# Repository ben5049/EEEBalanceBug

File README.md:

# EEEBalanceBug

### Abstract
A two-wheeled balancing robot was created to map a maze autonomously and calculate the shortest path. The maze was bounded by LED strips, and up to 3 differently coloured beacons could be placed around the maze beforehand. The beacons must be powered through a carefully optimised DC grid by solar power. There was a budget of £60 for the robot. An FPGA-based camera system must be used. Other optical sensors were permitted, but no other cameras. The methods employed include designing an advanced embedded system, hardware-based image processing, scalable cloud infrastructure and optimal energy distribution systems.

### Gantt Chart

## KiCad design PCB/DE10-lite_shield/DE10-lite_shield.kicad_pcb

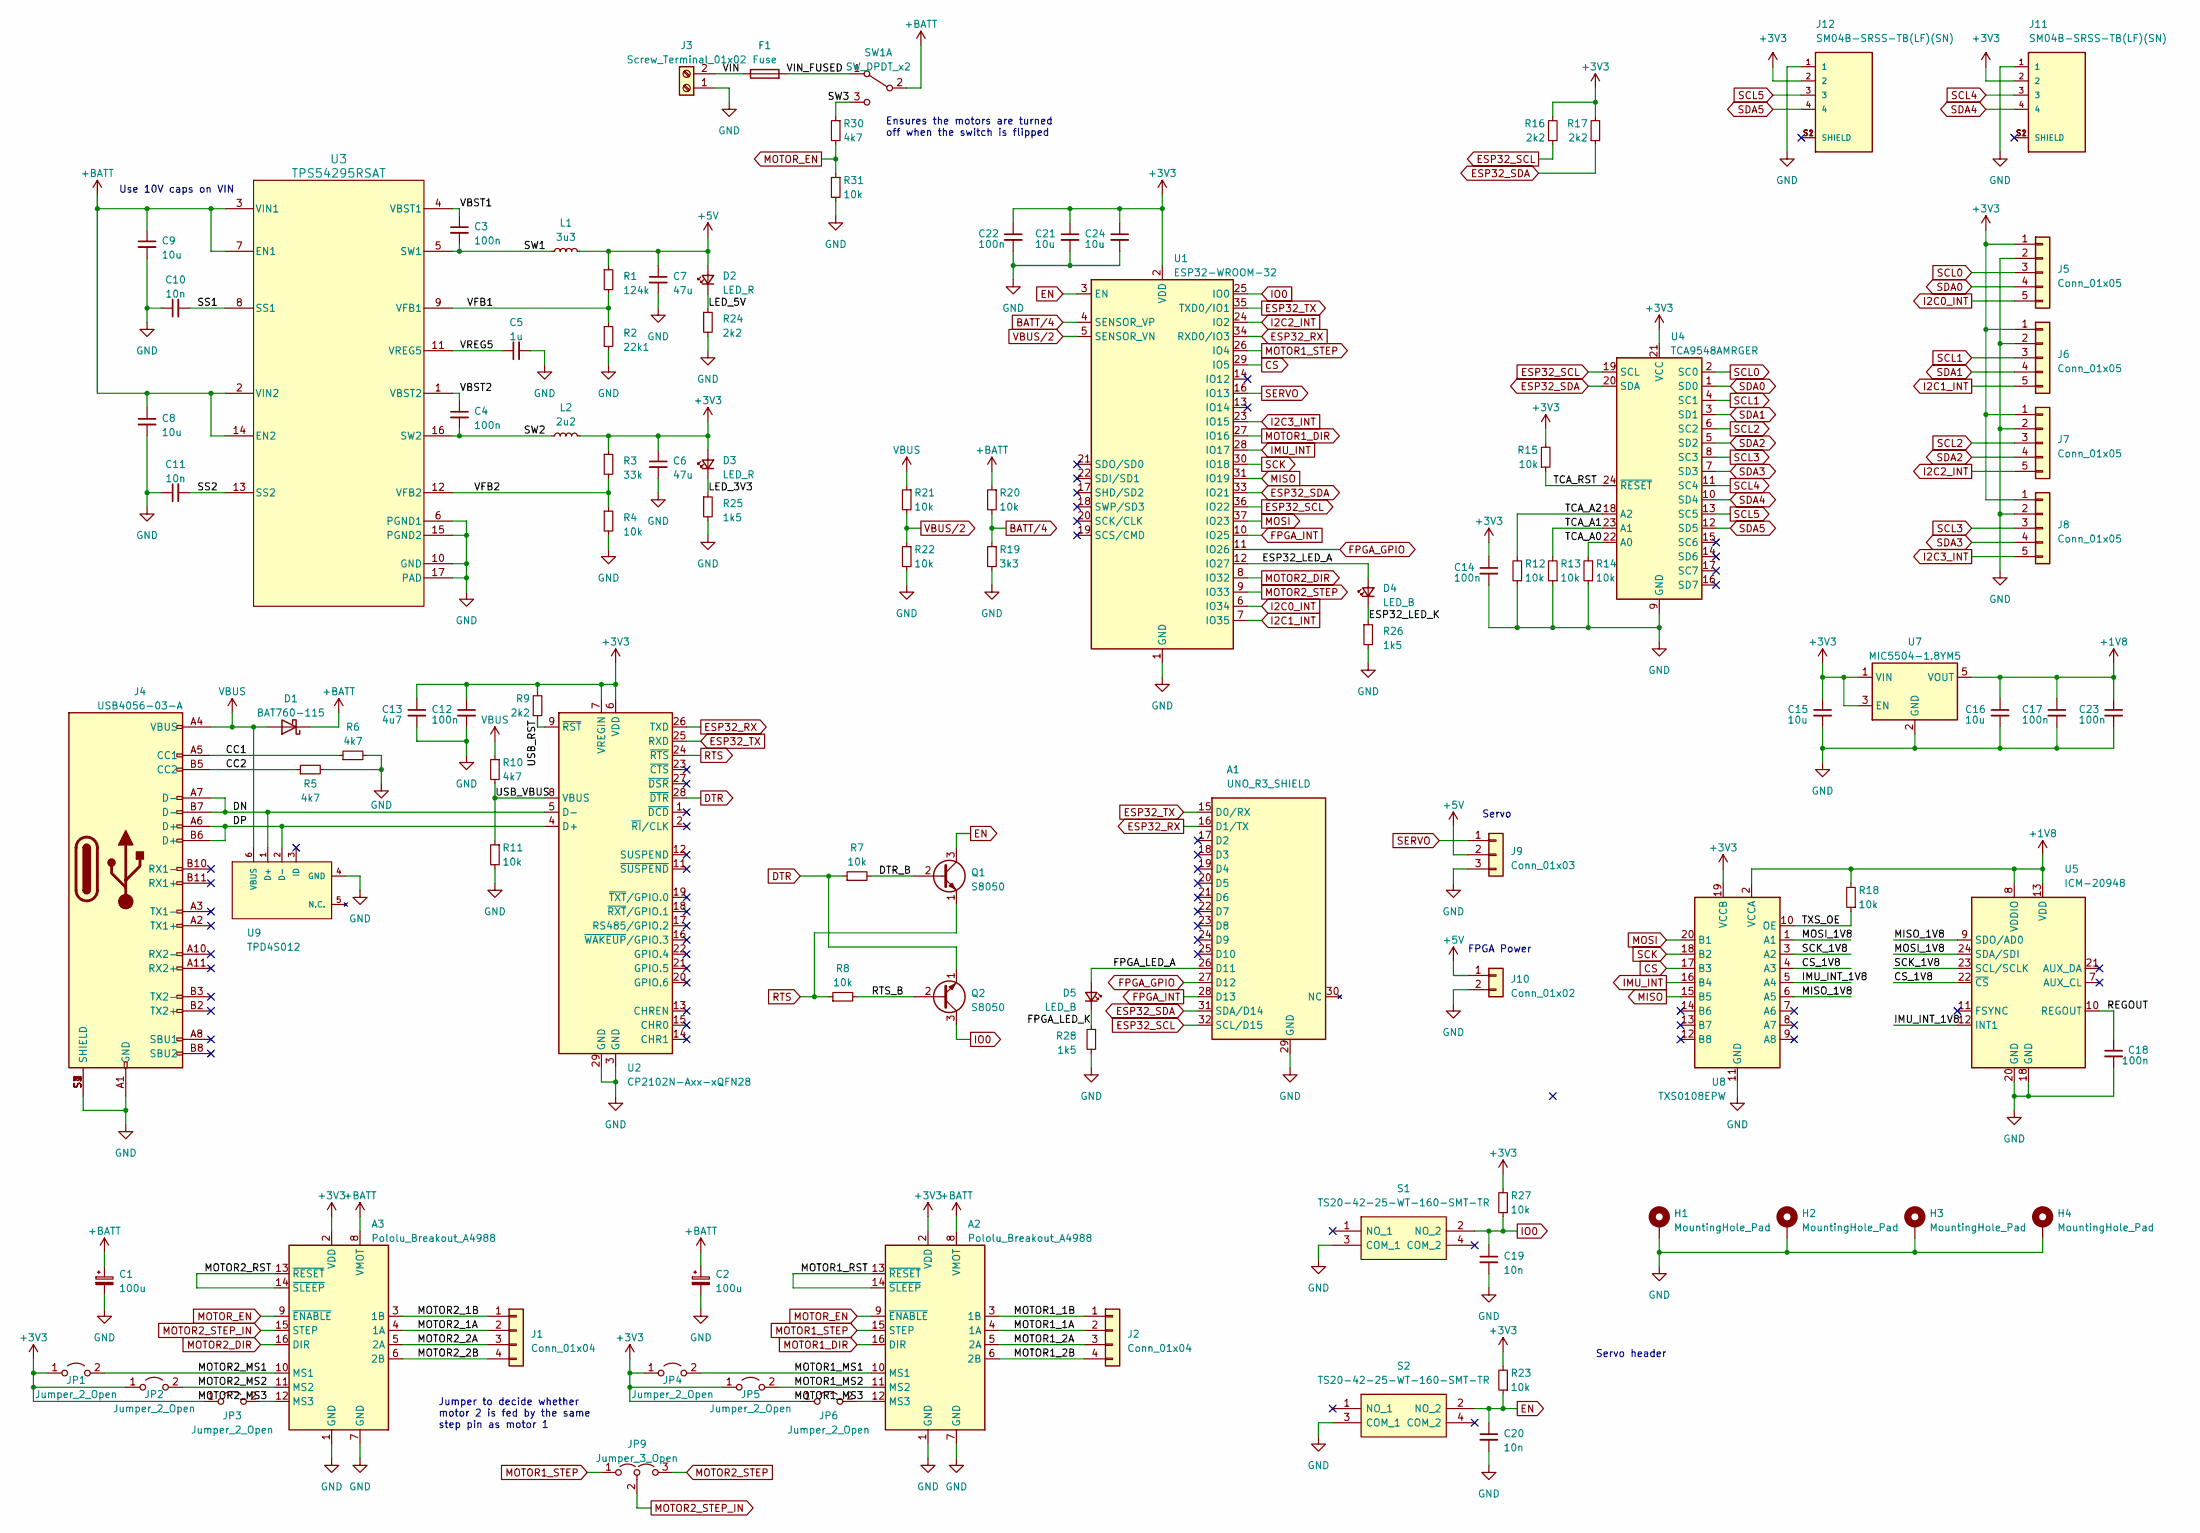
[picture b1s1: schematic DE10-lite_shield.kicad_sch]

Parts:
A1: UNO_R3_SHIELD
A2, A3: Pololu_Breakout_A4988; Pololu_Breakout-16_15.2x20.3mm
C1, C2: 100u; C_Rect_L4.0mm_W2.5mm_P2.50mm
C3, C4, C12, C14, C17, C18, C22, C23: 100n; C_0402_1005Metric
C5: 1u; C_0402_1005Metric
C6, C7: 47u; C_0805_2012Metric
C8, C9, C15, C16, C21, C24: 10u; C_0402_1005Metric
C10, C11, C19, C20: 10n; C_0402_1005Metric
C13: 4u7; C_0402_1005Metric
D1: BAT760-115; D_SOD-323
D2, D3: LED_R; LED_0603_1608Metric
D4, D5: LED_B; LED_0603_1608Metric
F1: Fuse; Fuseholder_Cylinder-5x20mm_Schurter_0031_8201_Horizontal_Op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
H1, H2, H3, H4: MountingHole_Pad; MountingHole_3.2mm_M3_DIN965_Pad
J1, J2: Conn_01x04; PinHeader_1x04_P2.54mm_Vertical
J3: Screw_Terminal_01x02; TerminalBlock_bornier-2_P5.08mm
J4: USB4056-03-A; GCT_USB4056-03-A_REVA; Mouser Part Number 640-USB4056-03-A
J5, J6, J7, J8: Conn_01x05; PinHeader_1x05_P2.54mm_Vertical
J9: Conn_01x03; PinHeader_1x03_P2.54mm_Vertical
J10: Conn_01x02; PinHeader_1x02_P2.54mm_Vertical
J11, J12: SM04B-SRSS-TB(LF)(SN); JST_SM04B-SRSS-TB(LF)(SN)
JP1, JP2, JP3, JP4, JP5, JP6: Jumper_2_Open; PinHeader_1x02_P2.54mm_Vertical
JP9: Jumper_3_Open; PinHeader_1x03_P2.54mm_Vertical
L1: 3u3; INDPM3630X200N
L2: 2u2; INDPM3630X200N
Q1: S8050; TO-92_Inline
Q2: S8050
R1: 124k; R_0402_1005Metric
R2: 22k1; R_0402_1005Metric
R3: 33k; R_0402_1005Metric
R4, R7, R8, R11, R12, R13, R14, R15, R18, R20, R21, R22, R23, R27, R31: 10k; R_0402_1005Metric
R5, R6, R10, R30: 4k7; R_0402_1005Metric
R9, R16, R17, R24: 2k2; R_0402_1005Metric
R19: 3k3; R_0402_1005Metric
R25, R26, R28: 1k5; R_0402_1005Metric
S1, S2: TS20-42-25-WT-160-SMT-TR; TS204225WT160SMTTR; Mouser Part Number 179-TS204225WT160SMT
SW1: SW_DPDT_x2; Toggle_switch
U1: ESP32-WROOM-32
U2: CP2102N-Axx-xQFN28; QFN-28-1EP_5x5mm_P0.5mm_EP3.35x3.35mm
U3: TPS54295RSAT
U4: TCA9548AMRGER; Texas_RGE0024C_EP2.1x2.1mm
U5: ICM-20948; InvenSense_QFN-24_3x3mm_P0.4mm
U7: MIC5504-1.8YM5; SOT-23-5
U8: TXS0108EPW; TSSOP-20_4.4x6.5mm_P0.65mm
U9: TPD4S012; SON50P100X145X60-6_TPD4S012DRYR; MPN TPD4S012DRYR

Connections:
+1V8: C16.1, C17.1, C23.1, R18.2, U5.8 (VDDIO), U5.13 (VDD), U7.5 (VOUT), U8.2 (VCCA)
+3V3: A2.2 (VDD), A3.2 (VDD), C6.1, C12.1, C13.1, C14.1, C15.1, C21.1, C22.1, C24.1, D3.2 (A), J5.1, J6.1, J7.1, J8.1, J11.2, J12.2, JP1.1 (A), JP2.1 (A), JP3.1 (A), JP4.1 (A), JP5.1 (A), JP6.1 (A), L2.2, R3.1, R9.2, R15.2, R16.2, R17.2, R23.2, R27.2, U1.2 (VDD), U2.6 (VDD), U2.7 (VREGIN), U4.21 (VCC), U7.1 (VIN), U7.3 (EN), U8.19 (VCCB); also elsewhere on the board
+5V: C7.1, D2.2 (A), J9.2, J10.1, L1.2, R1.1; also elsewhere on the board
+BATT: A2.8 (VMOT), A3.8 (VMOT), C1.1, C2.1, C8.1, C9.1, D1.1 (K), R20.1, SW1.2 (B), U3.2 (VIN2), U3.3 (VIN1), U3.7 (EN1), U3.14 (EN2)
/CC1: J4.A5 (CC1), R6.1
/CC2: J4.B5 (CC2), R5.1
/CS_1V8: U5.22 (~CS), U8.4 (A3)
/DN: J4.A7 (D-), J4.B7 (D-), U2.5 (D-), U9.1 (D+)
/DP: J4.A6 (D+), J4.B6 (D+), U2.4 (D+), U9.2 (D-)
/DTR_B: Q1.2 (B), R7.2
/ESP32_LED_A: D4.2 (A), U1.12 (IO27)
/ESP32_LED_K: D4.1 (K), R26.1
/FPGA_LED_A: A1.26 (D11), D5.2 (A)
/FPGA_LED_K: D5.1 (K), R28.1
/IMU_INT_1V8: U5.12 (INT1), U8.5 (A4)
/LED_3V3: D3.1 (K), R25.1
/LED_5V: D2.1 (K), R24.1
/MISO_1V8: U5.9 (SDO/AD0), U8.6 (A5)
/MOSI_1V8: U5.24 (SDA/SDI), U8.1 (A1)
/MOTOR1_1A: A2.4 (1A), J2.2
/MOTOR1_1B: A2.3 (1B), J2.1
/MOTOR1_2A: A2.5 (2A), J2.3
/MOTOR1_2B: A2.6 (2B), J2.4
/MOTOR1_MS1: A2.10 (MS1), JP4.2 (B)
/MOTOR1_MS2: A2.11 (MS2), JP5.2 (B)
/MOTOR1_MS3: A2.12 (MS3), JP6.2 (B)
/MOTOR1_RST: A2.13 (~RESET), A2.14 (~SLEEP)
/MOTOR2_1A: A3.4 (1A), J1.2
/MOTOR2_1B: A3.3 (1B), J1.1
/MOTOR2_2A: A3.5 (2A), J1.3
/MOTOR2_2B: A3.6 (2B), J1.4
/MOTOR2_MS1: A3.10 (MS1), JP1.2 (B)
/MOTOR2_MS2: A3.11 (MS2), JP2.2 (B); also elsewhere on the board
/MOTOR2_MS3: A3.12 (MS3), JP3.2 (B)
/MOTOR2_RST: A3.13 (~RESET), A3.14 (~SLEEP)
/REGOUT: C18.1, U5.10 (REGOUT)
/RTS_B: Q2.2 (B), R8.2
/SCK_1V8: U5.23 (SCL/SCLK), U8.3 (A2)
/SS1: C10.2, U3.8 (SS1)
/SS2: C11.2, U3.13 (SS2)
/SW1: C3.2, L1.1, U3.5 (SW1)
/SW2: C4.2, L2.1, U3.16 (SW2)
/SW3: R30.1, SW1.3 (C)
/TCA_A0: R14.2, U4.22 (A0)
/TCA_A1: R13.2, U4.23 (A1)
/TCA_A2: R12.2, U4.18 (A2)
/TCA_RST: R15.1, U4.24 (~RESET)
/TXS_OE: R18.1, U8.10 (OE)
/USB_RST: R9.1, U2.9 (~RST)
/USB_VBUS: R10.2, R11.1, U2.8 (VBUS)
/VBST1: C3.1, U3.4 (VBST1)
/VBST2: C4.1, U3.1 (VBST2)
/VFB1: R1.2, R2.1, U3.9 (VFB1)
/VFB2: R3.2, R4.1, U3.12 (VFB2)
/VIN: F1.1, J3.2
/VIN_FUSED: F1.2, SW1.1 (A)
/VREG5: C5.1, U3.11 (VREG5)
BATT/4: R19.1, R20.2, U1.4 (SENSOR_VP)
CS: U1.29 (IO5), U8.17 (B3)
DTR: Q2.1 (E), R7.1, U2.28 (~DTR)
EN: C20.1, Q1.3 (C), R23.1, S2.2 (NO_2), U1.3 (EN)
ESP32_RX: A1.16 (D1/TX), U1.34 (RXD0/IO3), U2.26 (TXD)
ESP32_SCL: A1.32 (SCL/D15), R16.1, U1.36 (IO22), U4.19 (SCL)
ESP32_SDA: A1.31 (SDA/D14), R17.1, U1.33 (IO21), U4.20 (SDA)
ESP32_TX: A1.15 (D0/RX), U1.35 (TXD0/IO1), U2.25 (RXD)
FPGA_GPIO: A1.27 (D12), U1.11 (IO26)
FPGA_INT: A1.28 (D13), U1.10 (IO25)
GND: A1.29 (GND), A2.1 (GND), A2.7 (GND), A3.1 (GND), A3.7 (GND), C1.2, C2.2, C5.2, C6.2, C7.2, C8.2, C9.2, C10.1, C11.1, C12.2, C13.2, C14.2, C15.2, C16.2, C17.2, C18.2, C19.2, C20.2, C21.2, C22.2, C23.2, C24.2, H1.1, H2.1, H3.1, H4.1, J3.1, J4.A1 (GND), J4.A12 (GND), J4.B1 (GND), J4.B12 (GND), J4.S1 (SHIELD), J4.S2 (SHIELD), J4.S3 (SHIELD), J4.S4 (SHIELD), J5.2, J6.2, J7.2, J8.2, J9.3, J10.2, J11.1, J12.1, R2.2, R4.2, R5.2, R6.2, R11.2, R12.1, R13.1, R14.1, R19.2, R22.2, R24.2, R25.2, R26.2, R28.2, R31.2, S1.3 (COM_1), S2.3 (COM_1), U1.1 (GND), U1.15 (GND), U1.38 (GND), U1.39 (GND), U2.3 (GND), U2.29 (GND), U3.6 (PGND1), U3.10 (GND), U3.15 (PGND2), U3.17 (PAD), U4.9 (GND), U4.25 (1EP), U5.18 (GND), U5.20 (GND), U7.2 (GND), U8.11 (GND), U9.4 (GND); also elsewhere on the board
I2C0_INT: J5.5, U1.6 (IO34)
I2C1_INT: J6.5, U1.7 (IO35)
I2C2_INT: J7.5, U1.24 (IO2)
I2C3_INT: J8.5, U1.23 (IO15)
IMU_INT: U1.28 (IO17), U8.16 (B4)
IO0: C19.1, Q2.3 (C), R27.1, S1.2 (NO_2), U1.25 (IO0)
MISO: U1.31 (IO19), U8.15 (B5)
MOSI: U1.37 (IO23), U8.20 (B1)
MOTOR1_DIR: A2.16 (DIR), U1.27 (IO16)
MOTOR1_STEP: A2.15 (STEP), JP9.1 (A), U1.26 (IO4)
MOTOR2_DIR: A3.16 (DIR), U1.8 (IO32)
MOTOR2_STEP: JP9.3 (B), U1.9 (IO33)
MOTOR2_STEP_IN: A3.15 (STEP), JP9.2 (C)
MOTOR_EN: A2.9 (~ENABLE), A3.9 (~ENABLE), R30.2, R31.1
RTS: Q1.1 (E), R8.1, U2.24 (~RTS)
SCK: U1.30 (IO18), U8.18 (B2)
SCL0: J5.3, U4.2 (SC0)
SCL1: J6.3, U4.4 (SC1)
SCL2: J7.3, U4.6 (SC2)
SCL3: J8.3, U4.8 (SC3)
SCL4: J11.3, U4.11 (SC4)
SCL5: J12.3, U4.13 (SC5)
SDA0: J5.4, U4.1 (SD0)
SDA1: J6.4, U4.3 (SD1)
SDA2: J7.4, U4.5 (SD2)
SDA3: J8.4, U4.7 (SD3)
SDA4: J11.4, U4.10 (SD4)
SDA5: J12.4, U4.12 (SD5)
SERVO: J9.1, U1.16 (IO13)
VBUS: D1.2 (A), J4.A4 (VBUS), J4.A9 (VBUS), J4.B4 (VBUS), J4.B9 (VBUS), R10.1, R21.1, U9.6 (VBUS)
VBUS/2: R21.2, R22.1, U1.5 (SENSOR_VN)

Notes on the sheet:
Jumper to decide whether motor 2 is fed by the same step pin as motor 1
Servo
Use 10V caps on VIN
FPGA Power
Ensures the motors are turned off when the switch is flipped
Servo header

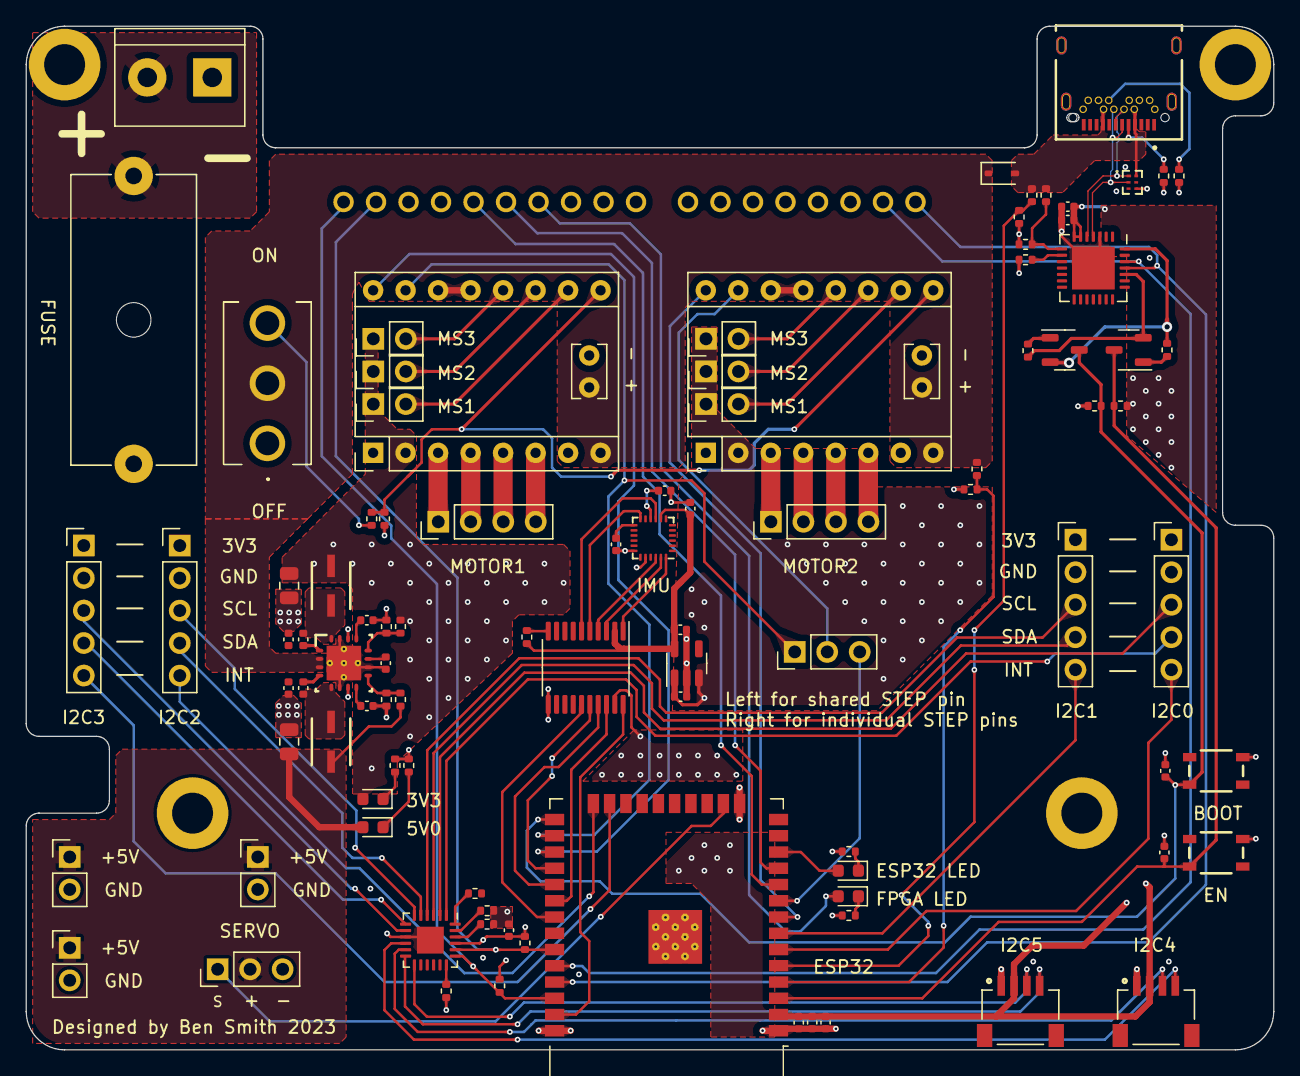
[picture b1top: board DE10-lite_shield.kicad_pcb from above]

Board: 4 copper layers, 97.5 x 80.0 mm, 103 parts (1 on the bottom side), 99 nets.

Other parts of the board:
J10#2, J10#3: Conn_01x02; PinHeader_1x02_P2.54mm_Vertical
locked: Jumper_2_Open; PinHeader_1x02_P2.54mm_Vertical

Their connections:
+3V3: locked.1 (A); also elsewhere on the board
+5V: J10#2.1, J10#3.1; also elsewhere on the board
/MOTOR2_MS2: locked.2 (B); also elsewhere on the board
GND: J10#2.2, J10#3.2; also elsewhere on the board

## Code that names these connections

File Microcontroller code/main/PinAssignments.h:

/*
Authors: Ben Smith
Date created: 28/05/23
Date updated: 28/05/23

Pin assignments for Group 1's EEEBalanceBug
*/

#ifndef PIN_ASSIGNMENTS_H
#define PIN_ASSIGNMENTS_H

//--------------------------------- PCB pins --------------------------------------------

/* Misc */
#define LED_BUILTIN 27
#define SERVO_PIN 13

/* Stepper motor control pins */
#define STEPPER_1_STEP 4
#define STEPPER_2_STEP 33
#define STEPPER_1_DIR 16
#define STEPPER_2_DIR 32

/* ADC */
#define VBAT 36 /* VBAT divided by 4 */
#define VBUS 39 /* VBUS divided by 2 */

/* UART */
#define ESP32_TX 1
#define ESP32_RX 3

/* SPI: IMU */
#define IMU_INT 17
#define IMU_MISO 19
#define IMU_MOSI 23
#define IMU_CS 5
#define IMU_SCK 18

/* I2C: FPGA, Multiplexer & ToF sensors */
#define I2C_SCL 22
#define I2C_SDA 21
#define FPGA_INT 25
#define FPGA_GPIO 26

#define I2C0_INT 34
#define I2C1_INT 35
#define I2C2_INT 2
#define I2C3_INT 15

/* Backwards compatibility */
#define IR_R_INT I2C1_INT
#define IR_L_INT I2C2_INT
#define TOF_R_INT I2C0_INT
#define TOF_L_INT I2C3_INT
#define STEPPER_STEP STEPPER_1_STEP
#define STEPPER_R_STEP STEPPER_2_DIR
#define STEPPER_L_STEP STEPPER_1_DIR
#define STEPPER_R_DIR STEPPER_2_DIR
#define STEPPER_L_DIR STEPPER_1_DIR

//--------------------------------- Stripboard pins -------------------------------------

// /* Stepper motor control pins */
// #define STEPPER_STEP 14
// #define STEPPER_MS2 25
// #define STEPPER_L_DIR 13
// #define STEPPER_R_DIR 27

// /* SPI: IMU */
// #define IMU_INT 15
// #define IMU_MISO 19
// #define IMU_MOSI 23
// #define IMU_CS 5
// #define IMU_SCK 18

// /* I2C: FPGA, Multiplexer & ToF sensors */
// #define I2C_SCL 22
// #define I2C_SDA 21
// #define TOF_L_INT 36
// #define TOF_R_INT 0


#endif

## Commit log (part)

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2023-06-12 Added buck converter layout image
2023-06-12 Recompiled for permanent flashing
2023-06-12 update how timestamps work bug fix
2023-06-12 bug fix estop again
2023-06-12 Added code to update pid values
2023-06-12 debugging
2023-06-12 updated offset value
2023-06-12 turn on debugging
2023-06-12 add debugging stuff
2023-06-12 more debugging
2023-06-12 bug fixing diagnostic data
2023-06-12 make mac address string
2023-06-12 reduce timeout for testing
2023-06-12 bug fix
2023-06-12 add better debugging prints turn off debugging
2023-06-12 Working Prototype
2023-06-12 update server ip update sercer setup script
2023-06-12 update server startup
2023-06-12 update servstart
2023-06-12 fix server startup
2023-06-12 IP change
2023-06-12 testing new fix
2023-06-12 undoing previous commit lol
2023-06-12 update server startup to change necessary file
2023-06-12 add automatic ip updater
2023-06-12 pof file
2023-06-12 Added pid turning over serial
2023-06-12 Added documentation
2023-06-12 update server startup and updateIP to take in argument from command line
2023-06-12 bug fix server startup
2023-06-12 update automatic ip update to include microcontroller
2023-06-12 IP Update
2023-06-12 rename microcontroller code folder fix updateip
2023-06-12 pof update
2023-06-12 bruh
2023-06-12 comment code for understandability & readability bug fix in dead reckoning
2023-06-12 Added PCB block diagram
2023-06-12 Deleted stuff
2023-06-13 speed controller implemented TODO: more tuning, gain scheduling
2023-06-13 Updated BOM to reflect purchased components
2023-06-13 Added resources for report
2023-06-13 Implemented priority ceiling protocol
2023-06-13 Moved data into subfolders and added IMU data
2023-06-13 Edited to allow sensor fusion data comparison
2023-06-13 update server start
2023-06-13 fix servstart
2023-06-13 fix servstart.sh
2023-06-13 Updated for beacon testing
2023-06-13 commented ip changing scripts
2023-06-13 added new data
2023-06-13 Formatting
2023-06-13 Added report document to README
2023-06-13 Added more debug print messages
2023-06-13 Added PCB outline testing image
2023-06-13 make IMU formatter
2023-06-13 add server state machine image
2023-06-13 Added beacon test data
2023-06-13 update server state machine png
2023-06-13 TOF image
2023-06-13 TOF data processing script
2023-06-13 Display rover position
2023-06-13 add ER diagram to report documentation
2023-06-13 fix server state machine report documentation
2023-06-14 Added FIR filter design image
2023-06-14 Added new ToF data
2023-06-14 Updated FIR filter
2023-06-14 fix dead reckoning add controller instructions to execute command
2023-06-14 Fixed FIR filters
2023-06-14 bug fix dead reckoning
2023-06-14 add debug logging and turn on debug
2023-06-14 ToF data will be filtered before sending
2023-06-14 Bugs found with sending commands
2023-06-14 turn on all leds temporarily
2023-06-14 Fixed filters and added ToF data
2023-06-14 camera zoom level
2023-06-14 microcontroller-server communcation working
2023-06-14 remove unnecessary files add logger
2023-06-14 actually commit into the database?
2023-06-14 change it to commit to db once not 5 times
2023-06-14 attempt to bug fix database commits
2023-06-14 db commit test
2023-06-14 fix test
2023-06-14 fixed db commits, removing test case
2023-06-14 remove logger
2023-06-14 update to make connection and cursor available in all endpoints
2023-06-14 add cursor back
2023-06-14 TOF out of bounds + README
2023-06-14 angular rate controller implemented
2023-06-15 add better error detection to server communication update timestamp to be float, not int add debugging for /client/allrovers
2023-06-15 Added basics of EEPROM code
2023-06-15 Updated thresholds for junction detection
2023-06-15 remove some debugging
2023-06-15 small bug fix
2023-06-15 turn off debug
2023-06-15 bug fix server communication
2023-06-15 update beacon angle queue usage
2023-06-15 stuff
2023-06-15 update beacon angle queue manageemnet
2023-06-15 force rover to update its position when spinning
2023-06-15 test only beacon detection
2023-06-15 add debugging
2023-06-15 fix server to use tremaux again update spinning to be resistant against repeated requests during spinning
2023-06-15 mem_init
2023-06-15 Cleanup
2023-06-15 gitignore + TOF formatter
2023-06-15 README
2023-06-15 turn off leds
2023-06-15 turn on led
2023-06-15 update server startup script fix led driver endpoints
2023-06-15 fpga config files
2023-06-15 updated speed control
2023-06-15 fix README
2023-06-15 add Report Writing Guidelines to README
2023-06-15 update to add where at to information sent by rover
2023-06-15 add battery readings to diagnostic data sent to server
2023-06-15 add angle setpoint queue, ready for angle controller
2023-06-15 update to send angle queue to controller
2023-06-15 bug fix tremaux's algorithm convert coordinates to mm remove error log
2023-06-15 Added front time of flight sensor code
2023-06-15 Revert "updated speed control"
    This reverts commit 0bff32192100efcc1a702c32fb10fd8156af42c5.
2023-06-15 allow float inputs from server response make server comms more robust and some bug fixes
2023-06-16 update server to print out angle setpoint
2023-06-16 make angle output look nicer
2023-06-16 more controller debug info
2023-06-16 update to see beacon angles
2023-06-16 TEST
2023-06-16 controller readouts
2023-06-16 add cumulative error
2023-06-16 send no instructions to rover
2023-06-16 MPPT formatter
2023-06-16 Remove Add rover button
2023-06-16 Upload LED_DRIVER code for each colour
2023-06-17 Updated pcb schematic
2023-06-17 Added 50Hzz FIR filter
2023-06-17 Acceleration based control
2023-06-17 bug fixes
2023-06-17 control finished, can be tuned better
2023-06-17 Gathered more IMU data
2023-06-17 Added DMP magnetometer option
2023-06-17 fixed bug in direction control
2023-06-18 IMU test data
2023-06-18 update triangulate to handle measurement drift
2023-06-18 Tidied up
2023-06-19 add idle and forward tests for rover to server remove unnecessary print statements
2023-06-19 Control decision matrix (report)
2023-06-19 Update control decision matrix
2023-06-19 add debug
2023-06-19 turn leds on
2023-06-19 update led drivers to handle low power change to forward test
2023-06-19 user inputs
2023-06-19 alternate between forward and idle
2023-06-19 testing again
2023-06-19 print things its sending
2023-06-19 tell it to go forward more often?
2023-06-19 Stuff and things
2023-06-19 More stuff
2023-06-19 meminit
2023-06-19 bug fix server comms - accessing dereferenced pointer
2023-06-19 fpga files
2023-06-19 more fpage congifs
2023-06-19 the return of the user input
2023-06-19 better ui
2023-06-19 hex file
2023-06-19 FPGA
2023-06-19 fpga config
2023-06-19 qwer
2023-06-19 atej
2023-06-19 Path control tuning
2023-06-19 Path Control PID needs tuning
2023-06-19 All IMU and ToF data is passed between tasks in queues
2023-06-20 Added and updated report files
2023-06-20 Tidied up code
2023-06-20 testing data and graphing code
2023-06-20 add debug info
2023-06-20 increase led timeout
2023-06-20 change beacon timeout
2023-06-20 keep beacons on 24/7
2023-06-20 tell rover to continuously spin
2023-06-20 chagne
2023-06-20 readd user input
2023-06-20 Revert "chagne"
    This reverts commit 23de4d856c5a51464247ff31603834e95631aead.
2023-06-20 change
2023-06-20 print position data
2023-06-20 chaneg to always send forwards
2023-06-20 make set number of commands
2023-06-20 update to spin
2023-06-20 add more idles before spinning
2023-06-20 Update commented version of the code
2023-06-20 Display negative coordinates
2023-06-20 change to go forward
2023-06-20 config
2023-06-20 debug and spin
2023-06-20 Edited PCB BOM
2023-06-20 FPGA Cam debug
2023-06-20 send rover forward
2023-06-20 PCB BOM Done
2023-06-20 Mechanical BoM
2023-06-20 Upadate Measurements
2023-06-20 Updated BOM stuff
2023-06-20 Updated image labels
2023-06-20 Created pre_release_package
2023-06-21 Add abstract to README.md
2023-06-21 make debugging nicer
2023-06-21 increasing node placement threshold remove unnecessary print
2023-06-21 Scaled mapping
2023-06-21 bug fix tremaux bug fix app
2023-06-21 change commands gto idle
2023-06-21 undo small fix
2023-06-21 Mirror screen
2023-06-21 npm Build
2023-06-21 add more tremaux testing
2023-06-21 change to use tremaux, not user inputs
2023-06-21 testing thresholding
2023-06-21 remove thresholding for 0,0
2023-06-21 Report figures
2023-06-21 reduce threshold and try to ignore thresholding at 0,0
2023-06-21 Added TaskBluetooth, fixed path control
2023-06-21 Bugs fixed
2023-06-21 Done i swear
2023-06-21 add thresholding fix for nodes
2023-06-21 added debugging for junction test
2023-06-21 add more debug
2023-06-21 Updated finish mapping
2023-06-21 Move Control test data
2023-06-21 added most recently placed node threshold detection
2023-06-21 improved debug info
2023-06-21 testing is finished flag for frontend
2023-06-21 add debug and led overriding
2023-06-21 bug fixes in tremaux better debug, overrides
2023-06-21 make yellow override global
2023-06-21 more debugx
2023-06-21 improve debug
2023-06-21 fixes
2023-06-21 add timeout check to /client/diagnostics
2023-06-21 add yaw
2023-06-22 More data for junction detection
2023-06-22 Rewrote junction detection both for FORWARD and SPIN
2023-06-22 add data debug
2023-06-22 add failsafe if branches or beacon angles not sent
2023-06-22 adds non-affective display data when paused or spinning
2023-06-22 add tree to database on timeout fix error in dijkstra
2023-06-22 testing why non-tof replay info is being added after a spin
2023-06-22 bug fix in tremaux
2023-06-22 Fixed navigating to replay + build
2023-06-22 fix attempting to put in same node into trees fix incorrect angle when going back
2023-06-22 set to go forward not spin at start
2023-06-22 update to stop repeated spinning at junctions
2023-06-22 debugging for diagnostics endpoint
2023-06-22 remove debugging, add failsafe for diagnostics
2023-06-22 add exception print
2023-06-22 bluetooth code for demo
2023-06-22 Junction detection data
2023-06-22 Various bug fixes
2023-06-22 update to remove unnecessary debug statements update triangulate with debug update tremaux with debug
2023-06-22 remove test data
2023-06-22 tremaux bug fix previously placed node
2023-06-22 Fixed replay diagnostics + build
2023-06-22 bug fix shortest path
2023-06-22 package - add POF and README
2023-06-22 are you happy now david?
2023-06-22 Rename Guide.md to README.md
2023-06-22 bug fix shortest path endpoint
2023-06-22 Spin task hysterisis working
2023-06-22 reduce threshold fix angle in go_back
2023-06-22 increase threshold
2023-06-22 bug fix dijkstra
2023-06-22 compile without bluetooth
2023-06-22 improved demo code
2023-06-22 spin control
2023-06-22 add fix for failure mode - stuck against wall during go back
2023-06-22 add debug for go back
2023-06-22 checking thresholding
2023-06-22 changed thresholds
2023-06-22 update thresholds
2023-06-22 imporve debug
2023-06-22 tell only turn angle
2023-06-22 slow down a lot
2023-06-22 stupid bug
2023-06-22 enable TaskExecuteCommand
2023-06-22 example turn
2023-06-22 stoof
2023-06-22 change angle to 90
2023-06-22 setpoint endpoint
2023-06-22 go back to using tremaux
2023-06-22 change tremaux to stop go back at junction remove print stmt
2023-06-22 change thresholds
2023-06-22 update go back for new junc detect
2023-06-22 turning 90 git push
2023-06-22 get back tremaux
2023-06-23 make it respin if it doesn't receive junctions by timeout
2023-06-23 align to 0 before spinning
2023-06-23 make sure it continues when trying to exit a junction
2023-06-23 add better debug info
2023-06-23 set to 0 before spin
2023-06-23 tell it to go forward when in whereat 4
2023-06-23 debug
2023-06-23 qpodjp aejfjapfj sdajfpdasjf
2023-06-23 pretty based ngl
2023-06-23 get rid of diagnostics
2023-06-23 check last seen timeouts
2023-06-23 more debug
2023-06-23 move timeout
2023-06-23 bug fix tremaux add demo endpoint
2023-06-23 rollback
2023-06-23 remove angle set before spin
2023-06-23 build
2023-06-24 Final organisation
